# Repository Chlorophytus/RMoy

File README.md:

# RMoy
Simple 12V 0.5A headphone amplifier convergent with the CMoy's design and philosophy. This is in early alpha stage but will be on Tindie soon.

## Background
Initially named "Seven Wonder", I realized that this converged with the famous CMoy headphone amplifier, freely available. I decided to open source it for others to enjoy.

## Specifications
- Gain is about 8x
- OPA2134 opamp (in the process of testing other opamps out there but this seems to be most happy)
- Nichicon UKA capacitors in the signal path (needed for coupling)
- The same magenta LED used in the BD139 Thing

## Caveats
- No knob like the CMoy has, computers and other devices have digital OS volume control. Use those.

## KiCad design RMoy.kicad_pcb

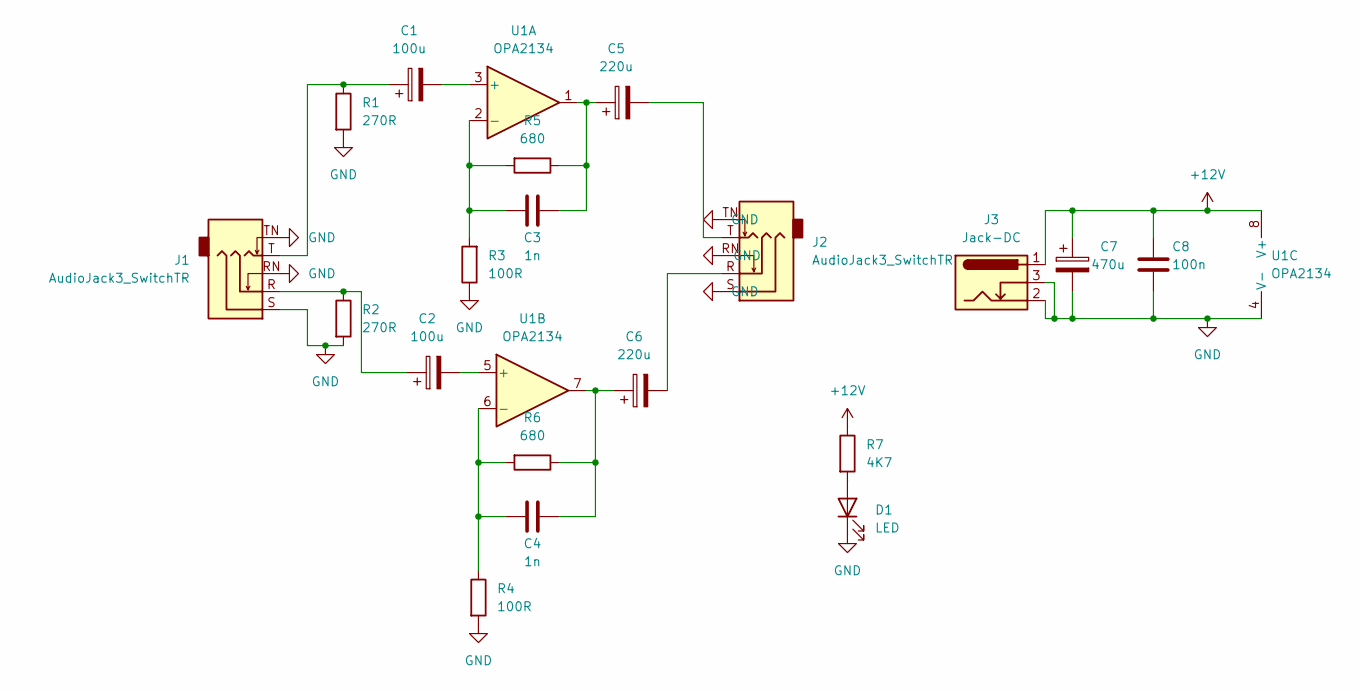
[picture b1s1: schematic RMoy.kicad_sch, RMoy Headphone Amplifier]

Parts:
C1, C2: 100u; CP_Radial_D8.0mm_P3.50mm
C3, C4: 1n; C_Disc_D5.0mm_W2.5mm_P5.00mm
C5, C6: 220u; CP_Radial_D8.0mm_P3.50mm
C7: 470u; CP_Radial_D10.0mm_P5.00mm
C8: 100n; C_Disc_D5.0mm_W2.5mm_P5.00mm
D1: LED; LED_D5.0mm
J1, J2: AudioJack3_SwitchTR; Jack_3.5mm_CUI_SJ1-3535NG_Horizontal_CircularHoles
J3: Jack-DC; BarrelJack_CUI_PJ-102AH_Horizontal
R1, R2: 270R; R_Axial_DIN0207_L6.3mm_D2.5mm_P10.16mm_Horizontal
R3, R4: 100R; R_Axial_DIN0207_L6.3mm_D2.5mm_P10.16mm_Horizontal
R5, R6: 680; R_Axial_DIN0207_L6.3mm_D2.5mm_P10.16mm_Horizontal
R7: 4K7; R_Axial_DIN0207_L6.3mm_D2.5mm_P10.16mm_Horizontal
U1: OPA2134; DIP-8_W7.62mm_Socket

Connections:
+12V: C7.1, C8.2, J3.1, R7.1, U1.8 (V+)
GND: C7.2, C8.1, D1.1 (K), J1.RN, J1.S, J1.TN, J2.RN, J2.S, J2.TN, J3.2, J3.3, R1.2, R2.2, R3.1, R4.2, U1.4 (V-)
unnamed: C1.1, J1.T, R1.1
unnamed: C2.1, J1.R, R2.1
unnamed: C3.2, C5.1, R5.1, U1.1
unnamed: C4.2, C6.1, R6.1, U1.7
unnamed: C5.2, J2.T
unnamed: C6.2, J2.R
unnamed: D1.2 (A), R7.2
unnamed: C1.2, U1.3 (+)
unnamed: C3.1, R3.2, R5.2, U1.2 (-)
unnamed: C2.2, U1.5 (+)
unnamed: C4.1, R4.1, R6.2, U1.6 (-)

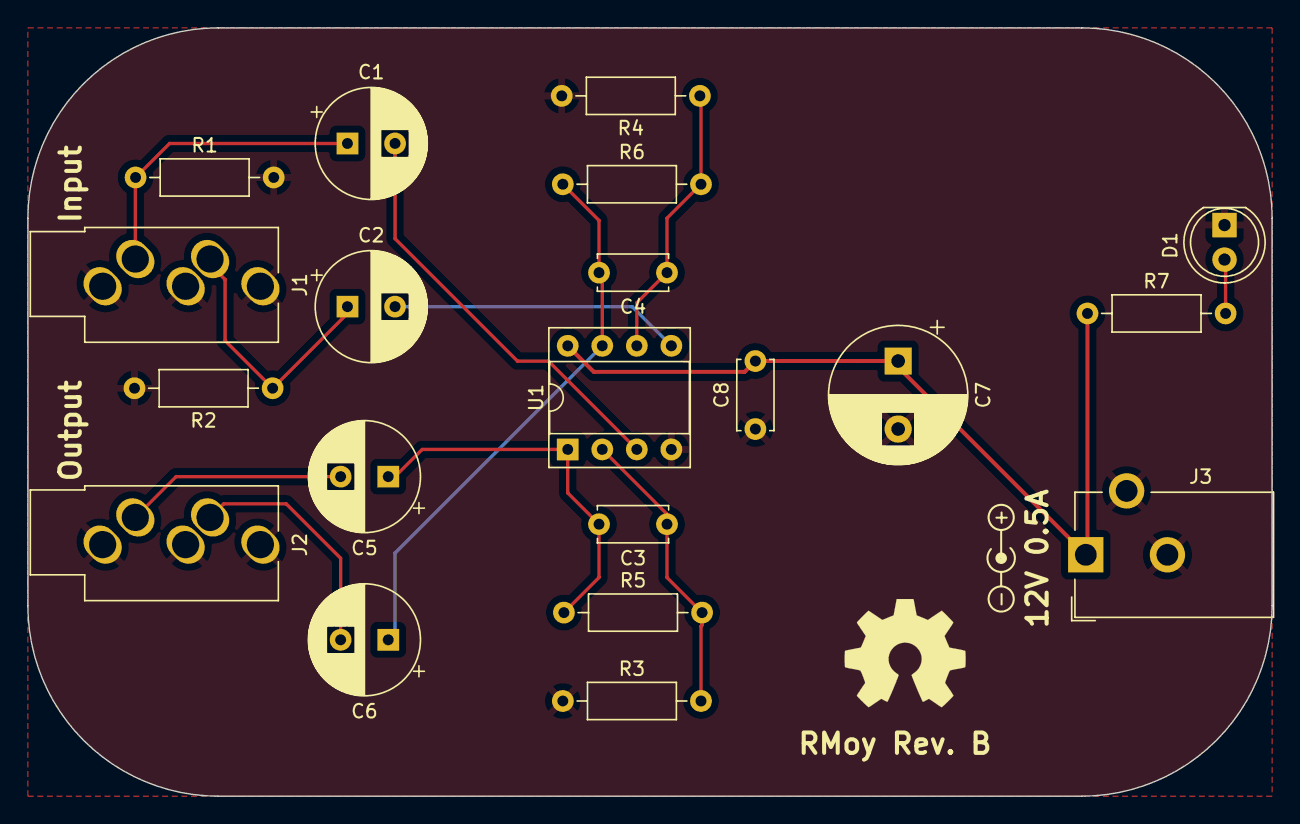
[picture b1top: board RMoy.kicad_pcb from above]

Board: 2 copper layers, 91.5 x 56.5 mm, 20 parts (0 on the bottom side), 13 nets.

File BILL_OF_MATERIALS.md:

# Bill of Materials

You should populate U1 with a Burr Brown/Texas Instruments OPA2134PA.

It is recommended to use a 12V 500mA center-positive power adapter.

## Capacitors

- `C1`/`C2`: Nichicon UKA1H101MPD - 100µF op-amp input coupling
- `C3`/`C4`: Murata RDE5C1H102J0K1H03B - 1nF op-amp pole splitting
- `C5`/`C6`: Nichicon UKA1V221MPD - 220µF op-amp output coupling
- `C7`: Chemi-Con EKZN250ELL471MJC5S - 470µF power coupling
- `C8`: Murata RDE5C1H104J2K1H03B - 100nF power coupling

## Resistors

- `R1`/`R2` - YAGEO MFR-25FBF52-270R - path for audio input to ground
- `R3`/`R4` - YAGEO MFR-25FBF52-100R - path for feedback to ground
- `R5`/`R6` - YAGEO MFR-25FBF52-680R - path for feedback to U1
- `R7` - YAGEO MFR-25FBF52-4K7 - LED current limiting resistor

## Miscellaneous Components

- `J1`/`J2` - Same Sky SJ1-3535 - stereo headphones in/out jacks
- `J3` - Same Sky PJ-102AH - DC power jack
- `U1` - TE Connectivity 2485264-1 - 8-DIP socket for op-amp
- `D1` - Kingbright WP7113VRVC1C - LED power indicator

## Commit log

2022-01-12 Add RMoy Rev.A files
2022-01-12 Remove unneeded netlist
2022-03-25 Create LICENSE after forgetting
2024-10-05 add revised parts list
    TODO: C1/C2/C5/C6 have not been modified, are they obsolete?
2024-10-05 2024 copyright
2024-10-05 C1/C2 are now 100µF non-EOL parts
2024-10-05 PCB is reworked
2024-10-06 update BOM to add actual resistor SKUs
2024-10-06 rev.B try
2024-10-16 clarify README a bit
